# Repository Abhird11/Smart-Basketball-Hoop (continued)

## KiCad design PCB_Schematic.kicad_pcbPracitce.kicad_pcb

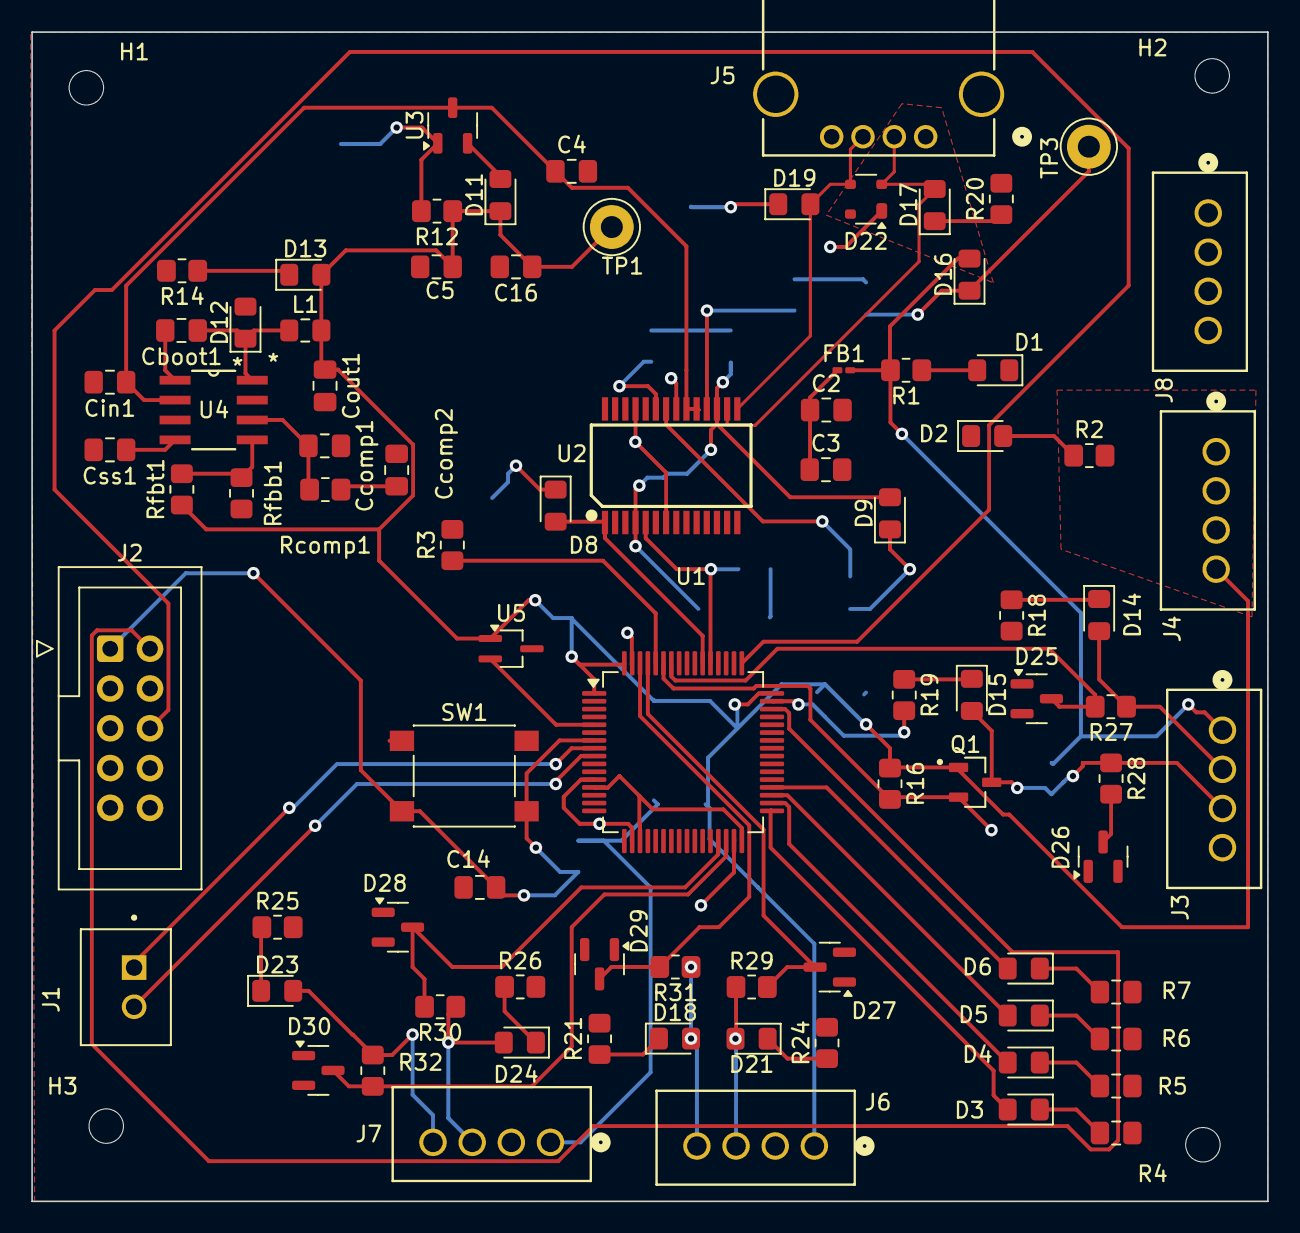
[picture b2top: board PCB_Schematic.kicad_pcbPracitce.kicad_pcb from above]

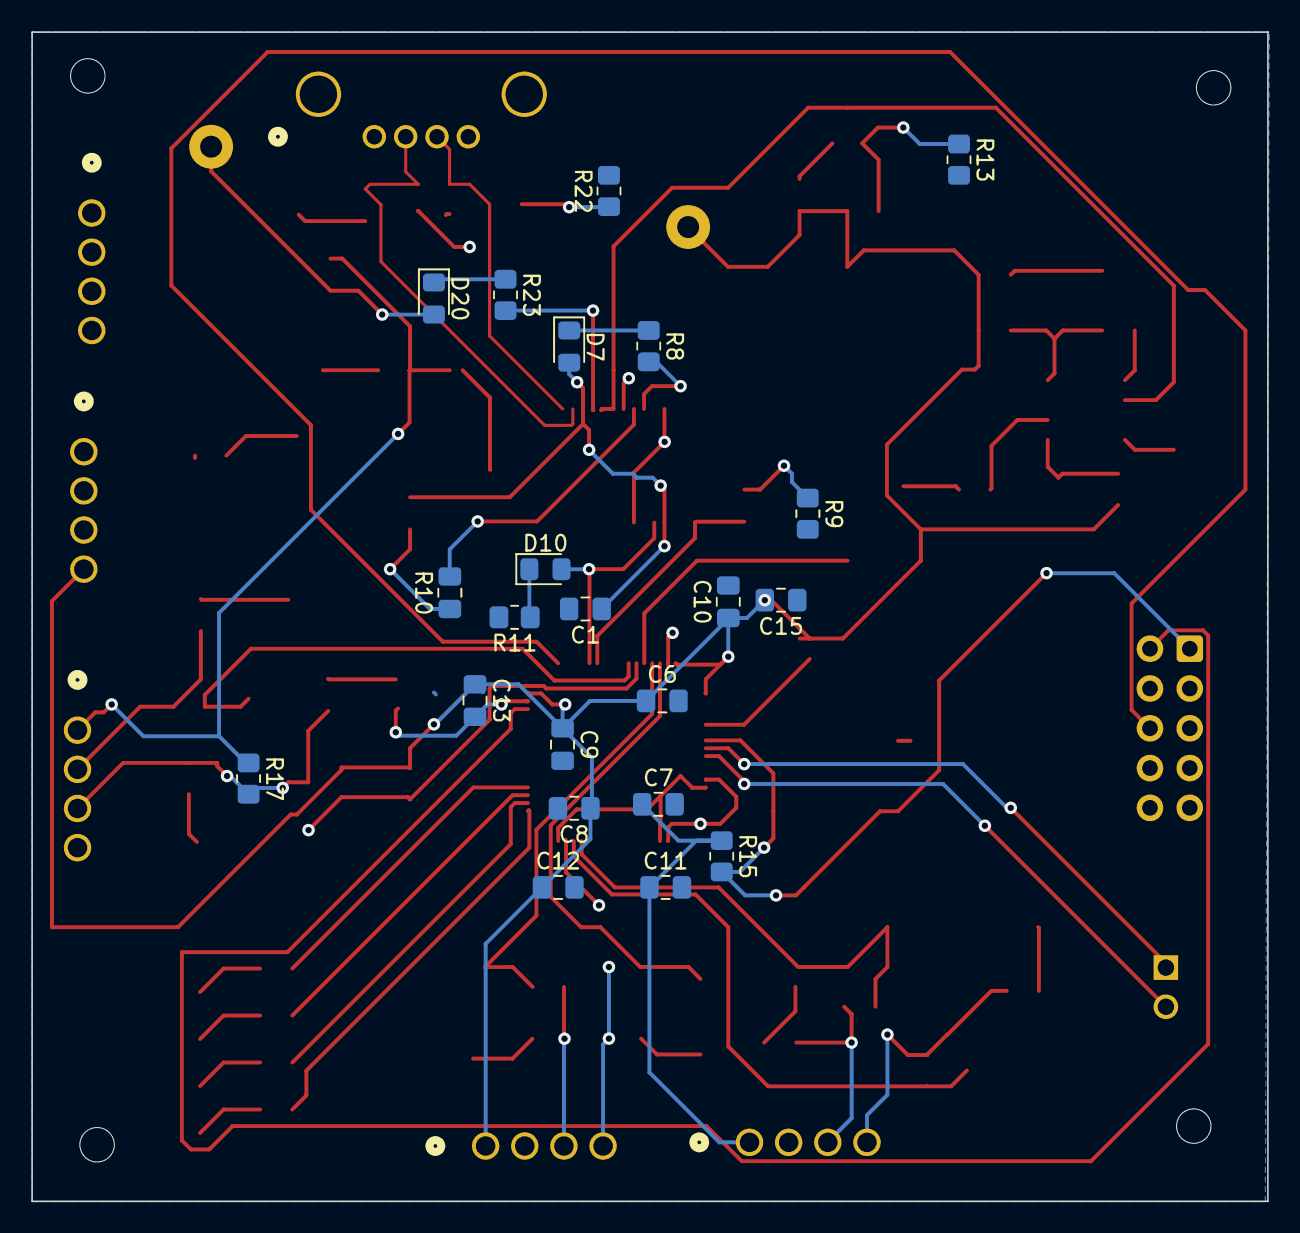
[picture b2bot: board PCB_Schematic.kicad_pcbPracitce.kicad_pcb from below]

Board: 2 copper layers, 78.9 x 74.7 mm, 110 parts (22 on the bottom side), 64 nets.

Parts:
C1, C2: 100 nF; C_0805_2012Metric_Pad1.18x1.45mm_HandSolder
C3, C10, C12: 4.7 uF; C_0805_2012Metric_Pad1.18x1.45mm_HandSolder
C4: 10 uF; C_0805_2012Metric_Pad1.18x1.45mm_HandSolder
C5: 100 uF; C_0805_2012Metric_Pad1.18x1.45mm_HandSolder
C6, C7, C8, C9, C16: .1 uF; C_0805_2012Metric_Pad1.18x1.45mm_HandSolder
C11: 10 nF; C_0805_2012Metric_Pad1.18x1.45mm_HandSolder
C13: 1 uF; C_0805_2012Metric_Pad1.18x1.45mm_HandSolder
C14: .1uF; C_0805_2012Metric_Pad1.18x1.45mm_HandSolder
C15: 0.1uF; C_0805_2012Metric_Pad1.18x1.45mm_HandSolder
Cboot1: 100 nF; C_0805_2012Metric_Pad1.18x1.45mm_HandSolder
Ccomp1: 10 pF; C_0805_2012Metric_Pad1.18x1.45mm_HandSolder
Ccomp2: 2.7 nF; C_0805_2012Metric_Pad1.18x1.45mm_HandSolder
Cin1: 10 uF; C_0805_2012Metric_Pad1.18x1.45mm_HandSolder
Cout1: 47 uF; C_0805_2012Metric_Pad1.18x1.45mm_HandSolder
Css1: 8.2 nF; C_0805_2012Metric_Pad1.18x1.45mm_HandSolder
D1, D2, D3, D4, D5, D6, D7, D9, D14, D20, D21, D23: LED_Blue; LED_0805_2012Metric_Pad1.15x1.40mm_HandSolder
D8, D17: LED_Green; LED_0805_2012Metric_Pad1.15x1.40mm_HandSolder
D10, D13, D15, D18, D19, D24: LED_Red; LED_0805_2012Metric_Pad1.15x1.40mm_HandSolder
D11, D12, D16: BAT60JFILM; D_0805_2012Metric_Pad1.15x1.40mm_HandSolder
D22: PRTR5V0U2X; SOT-143
D25, D26, D27, D28, D29, D30: BZX84Cxx; SOT-23
FB1: FerriteBead; L_0201_0603Metric_Pad0.64x0.40mm_HandSolder
H1, H2, H3, H4: MountingHole; MountingHole_2.2mm_M2
J1: Conn_01x02_Pin; 2Pin
J2: Programming Header; IDC-Header_2x05_P2.54mm_Vertical
J3: Ultrasonic; CONN_B4B-XH-A_JSTProject
J4: Power_Connector; CONN_B4B-XH-A_JSTProject
J5: USB_A; Project_USB
J6: IMU_1; CONN_B4B-XH-A_JSTProject
J7: IMU_2; CONN_B4B-XH-A_JSTProject
J8: SDOAG_Connector; CONN_B4B-XH-A_JSTProject
L1: 6.8 uH; L_0805_2012Metric_Pad1.15x1.40mm_HandSolder
Q1: BSS138; Project_BSS
R1, R2, R16, R17: 10k; R_0805_2012Metric_Pad1.20x1.40mm_HandSolder
R3, R15: 100K; R_0805_2012Metric_Pad1.20x1.40mm_HandSolder
R4, R5, R6, R7, R10: 270; C_0805_2012Metric_Pad1.18x1.45mm_HandSolder
R8: 270; R_0805_2012Metric_Pad1.20x1.40mm_HandSolder
R9, R11, R12, R14, R18, R19, R20, R21, R22, R23, R24, R25, R26: 150; R_0805_2012Metric_Pad1.20x1.40mm_HandSolder
R13: 220; R_0805_2012Metric_Pad1.20x1.40mm_HandSolder
R27, R28, R29, R30, R31, R32: 20; R_0805_2012Metric_Pad1.20x1.40mm_HandSolder
Rcomp1: 13.7 k; R_0805_2012Metric_Pad1.20x1.40mm_HandSolder
Rfbb1: 3.24 k; R_0805_2012Metric_Pad1.20x1.40mm_HandSolder
Rfbt1: 10.2 k; R_0805_2012Metric_Pad1.20x1.40mm_HandSolder
SW1: Reset Switch; SW_SPST_PTS645
TP1: 3.3V TP; TestPoint_Loop_D3.50mm_Drill1.4mm_Beaded
TP3: 5V TP; TestPoint_Loop_D3.50mm_Drill1.4mm_Beaded
U1: STM32F091RCTx; LQFP-64_10x10mm_P0.5mm
U2: FT232RL; Project_FT232
U3: LM1117MP-ADJ; SOT-23-3
U4: TPS54331QDRQ1; Project_TPS
U5: MAX7375AXR805; SOT-323_SC-70_Handsoldering

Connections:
+3.3V: C5.1, C6.1, C7.1, C8.1, C9.1, C10.1, C11.1, C12.1, C13.1, C15.2, C16.1, Cout1.1, D11.1 (K), D13.2 (A), J4.1, J4.2, J4.3, J4.4, J6.1, J7.1, L1.2, Q1.1 (G), R2.2, R12.1, R15.1, R16.1, Rfbt1.1, TP1.1, U1.1 (VBAT), U1.13 (VDDA), U1.19 (VDD), U1.32 (VDD), U1.48 (VDDIO2), U1.64 (VDD), U5.1 (V+)
+5V: C4.1, Cin1.1, D16.2 (A), D22.4 (VCC), FB1.2, J3.1, J5.1 (VBUS), R1.2, R17.1, U2.19 (~RESET), U2.20 (VCC), U3.3 (VI), U4.2 (VIN)
/BOOT0: R3.1, U1.60 (PF11)
/DEBUG1: D3.2 (A), U1.33 (PB12)
/DEBUG2: D4.2 (A), U1.34 (PB13)
/DEBUG3: D5.2 (A), U1.35 (PB14)
/DEBUG4: D6.2 (A), U1.36 (PB15)
/Echo3.3V: Q1.2 (S), R16.2, U1.59 (PB7)
/Echo5V: D26.3 (K), R28.2
/Echo5VE: D15.2 (A), J3.3, Q1.3 (D), R17.2, R28.1
/NRST: C14.1, J2.1, R15.2, SW1.2, U1.7 (NRST)
/OSC_IN: U1.5 (PF0), U5.2 (CLOCK)
/PC0: J1.1, U1.8 (PC0)
/PC1: J1.2, U1.9 (PC1)
/RXD: D10.2 (A), U1.53 (PC12), U2.5 (RXD)
/SCL1: D27.3 (K), R29.2, U1.61 (PB8)
/SCL1E: D21.2 (A), J6.3, R29.1
/SCL2: D28.3 (K), R30.2, U1.29 (PB10)
/SCL2E: D24.2 (A), J7.3, R30.1
/SDA1: D29.3 (K), R31.2, U1.62 (PB9)
/SDA1E: D18.2 (A), J6.4, R31.1
/SDA2: D30.3 (K), R32.2, U1.30 (PB11)
/SDA2E: D23.2 (A), J7.4, R32.1
/SWCLK_IN: J2.6, U1.49 (PA14)
/SWDIO_IN: J2.2, U1.46 (PA13)
/TXD: D8.2 (A), U1.54 (PD2), U2.1 (TXD)
/Trig: D25.3 (K), R27.2, U1.58 (PB6)
/TrigE: D14.2 (A), J3.2, R27.1
/USB UART Comm/VCCIO: C1.1, D7.2 (A), D9.2 (A), U2.4 (VCCIO), U2.17 (3V3OUT)
/USBD+: D19.2 (A), D22.3 (I/O2), J5.3 (D+), U2.15 (USBD+)
/USBD-: D17.2 (A), D22.2 (I/O1), J5.2 (D-), U2.16 (USBD-)
GND: C1.2, C2.2, C3.2, C4.2, C5.2, C6.2, C7.2, C8.2, C9.2, C10.2, C11.2, C12.2, C13.2, C14.2, C15.1, C16.2, Ccomp1.2, Ccomp2.2, Cin1.2, Cout1.2, Css1.2, D1.1 (K), D2.1 (K), D12.2 (A), D22.1 (GND), D25.1 (A), D26.1 (A), D27.1 (A), D28.1 (A), D29.1 (A), D30.1 (A), J2.3, J2.4, J3.4, J5.4 (GND), J6.2, J7.2, J8.1, J8.2, J8.3, J8.4, R3.2, R4.2, R5.2, R6.2, R7.2, R9.2, R11.2, R13.2, R14.2, R18.2, R19.2, R20.2, R21.2, R22.2, R23.2, R24.2, R25.2, R26.2, Rfbb1.2, SW1.1, U1.12 (VSSA), U1.18 (VSS), U1.31 (VSS), U1.47 (VSS), U1.63 (VSS), U2.7 (GND), U2.18 (GND), U2.21 (GND), U2.25 (AGND), U2.26 (TEST), U4.7 (GND), U5.3 (GND)
unnamed: C2.1, C3.1, FB1.1
unnamed: Ccomp2.1, Rcomp1.2
unnamed: D1.2 (A), R1.1
unnamed: D2.2 (A), R2.1
unnamed: D3.1 (K), R4.1
unnamed: D4.1 (K), R5.1
unnamed: D5.1 (K), R6.1
unnamed: D6.1 (K), R7.1
unnamed: D7.1 (K), R8.1
unnamed: D8.1 (K), R9.1
unnamed: D9.1 (K), R10.1
unnamed: D10.1 (K), R11.1
unnamed: D11.2 (A), U3.2 (VO)
unnamed: Cboot1.1, D12.1 (K), L1.1, U4.8 (PH)
unnamed: D13.1 (K), R14.1
unnamed: D14.1 (K), R18.1
unnamed: D15.1 (K), R19.1
unnamed: D16.1 (K), D20.2 (A), TP3.1
unnamed: D17.1 (K), R20.1
unnamed: D18.1 (K), R21.1
unnamed: D19.1 (K), R22.1
unnamed: D20.1 (K), R23.1
unnamed: D21.1 (K), R24.1
unnamed: D23.1 (K), R25.1
unnamed: D24.1 (K), R26.1
unnamed: R8.2, U2.23 (CBUS0)
unnamed: R10.2, U2.22 (CBUS1)
unnamed: R12.2, R13.1, U3.1 (ADJ)
unnamed: Cboot1.2, U4.1 (BOOT)
unnamed: Ccomp1.1, Rcomp1.1, U4.6 (COMP)
unnamed: Css1.1, U4.4 (SS)
unnamed: Rfbb1.1, Rfbt1.2, U4.5 (VSENSE)

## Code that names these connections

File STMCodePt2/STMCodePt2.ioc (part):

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Mcu.Name=STM32F091R(B-C)Tx
Mcu.Package=LQFP64
Mcu.UserName=STM32F091RCTx
PA1.Signal=GPIO_Output
PA10.Mode=I2C
PA10.Signal=I2C1_SDA
PA11.Mode=I2C
PA11.Signal=I2C2_SCL
PA12.Mode=I2C
PA12.Signal=I2C2_SDA
PA2.Signal=GPIO_Input
PA4.Mode=Asynchronous
PA4.Signal=USART6_TX
PA5.Mode=Asynchronous
PA5.Signal=USART6_RX
PA9.Mode=I2C
PA9.Signal=I2C1_SCL
PB12.Signal=GPIO_Output
PB4.Mode=Asynchronous
PB4.Signal=USART5_RX
PB6.Signal=GPIO_Output
PB7.Signal=GPIO_Input
PC12.Mode=Asynchronous
PC12.Signal=USART5_TX
PC9.Signal=GPIO_Output
PD2.Signal=GPIO_Output
board=custom

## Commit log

2024-09-18 yolo stuff
2024-09-18 Create LICENSE
2024-09-19 STM code
2024-09-19 include for HAL Driver
2024-09-24 Updated Sam Test
2024-09-24 Sam Couple Cum Cleanup Changes
2024-09-24 Sam Couple Gay Changes
2024-09-25 More Updates
2024-09-25 Add some decaps for 3.3V
2024-09-25 Stuff
2024-09-25 recent changes
2024-09-25 new stuff
2024-09-26 PCB Schematic Additions
2024-09-26 changes Sam
2024-09-30 Sam more bs
2024-10-01 more
2024-10-01 More changes
2024-10-01 More BS ches
2024-10-01 cookies
2024-10-01 no errors
2024-10-01 new caps
2024-10-01 1206 changed 0805
2024-10-01 minor footprint changes
2024-10-01 OSC_IN pin change, add BOOT0, just copy programming header from schematic
2024-10-01 new ESD and footprints
2024-10-02 subsheets added
2024-10-02 remove un-needed program header circuitry, add debug LEDs, add USB ESD, add shcotty for LM117
2024-10-02 more cap changes
2024-10-02 starter PCB
2024-10-02 PCB changes
2024-10-02 layout more
2024-10-04 old stuff
2024-10-07 Working IMU code
2024-10-09 routing v1
2024-10-09 added ground poly and remember you cannot have vias inside pads
2024-10-09 added testpoints to schematic for important sigs
2024-10-09 solved some errors
2024-10-09 done
2024-10-09 17 errors
2024-10-09 5 errors left
2024-10-09 5 errors
2024-10-10 5 error
2024-10-10 going to set up for review
2024-10-10 submit to TA
2024-10-10 vias
2024-10-10 traces final
2024-10-10 sam changes
2024-10-10 new edits
2024-10-11 ready pcb
2024-10-11 new buck
2024-10-11 updated stuff
2024-10-12 sam some changes
2024-10-14 removed LEDs on IMU and ultrasonic
2024-10-14 need change
2024-10-14 mounting holes locations
2024-10-14 outdated
2024-10-14 updated fp
2024-10-14 BOM done
2024-10-14 footprint verf
2024-10-14 footprint
2024-10-14 footprints
2024-10-15 new FB
2024-10-15 buck
2024-10-15 sam work more
2024-10-16 remove acute
2024-10-16 added output plane for buck
2024-10-16 added outplane for buck
2024-10-16 most done
2024-10-16 one error
2024-10-16 final sending for review
2024-10-18 nothing
2024-10-18 slight alter
2024-10-18 unpack.py
2024-10-19 some changes
2024-10-19 merged code (in progress)
2024-10-21 finish touches
2024-10-22 need to make more changes
2024-10-23 finished fr
2024-10-23 gerbers
2024-10-23 done fr
2024-11-15 imu testing
2024-11-16 Updated STM code and laptop code
2024-11-17 new code
2024-11-18 updated code
2024-12-04 server.py
2024-12-04 gui update
